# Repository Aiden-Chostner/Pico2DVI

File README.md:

# Pico2DVI

## Story
Recently, I began exploring circuit design, and I liked the idea of creating my own custom graphics card because it sounded like a fun project. After some back and forth of choosing requirements for the GPU, I settled on using a Raspberry Pi Pico as the main processor. It already had a graphics library made for it, which would make adding HDMI support simple. I saw [PicoDVI by Luke Wren](https://github.com/Wren6991/PicoDVI), but I wanted to add more RAM and some extra capabilities. I added 32MB of VRAM (Video Random Access Memory), which is about 250 times less capacity and 36 million times slower than the memory on a modern GPU. (As you can probably tell, I was not going for speed.) The Pico also has Wi-Fi and extra general-purpose pins. That means the card can take in user inputs like a keyboard and output data in ways other than just a display. It can also fetch data (e.g stock market information) from the Internet. I prioritized versatility over speed.

## Specs
* RP2350 Core
* 32 MB VRAM
* HDMI DVI
* Extra I/O
* Subzero Cooler
* Wifi 2.4 GHz

## If you want to build it, I have an [instructables page](https://www.instructables.com/Pico2DVI-the-Graphics-Card-You-Can-Build-Yourself/)!

## Schematic

### I went through a couple variations changing:
* Memory
* Cooling
* Extra I/O Pins

## PCB

### Impedance 
The hardest part about designing the PCB was getting the DVI traces correct. At the clock speeds that DVI runs at, electricity starts to behave unpredictably. The signals start to degrade to the point where they cannot be properly received by the monitor. To correct the signals, I needed to use the impedance calculator in KiCad. It took a couple of attempts through trial and error to correctly calculate the impedance needed for DVI.

## Subzero Cooler

### Peltier Module
For HDMI to work properly the Raspberry Pi needs to be overclocked. This generates excess heat so I designed a subzero cooler. It uses a Peltier module which uses electricity to move heat from one side to the other. Using one on the GPU allows the core temperature to be lower than the room it is in.

## Memory

### Bitbanging
The protocol the memory chips use is called SPI. (Serial Peripheral Interface) Each chip uses four wires on a shared bus with every other chip, which saves valuable GPIO pins from the Raspberry Pi. I decided to bitbang the signals and code them manually. Each instruction, like reading or writing, has a different timing diagram like the one above. I made a function that had modular instructions so I did not have to manually code each one.

# Projects!
## Hello World

When I first got the graphics card working I was so excited. It took four revisions to get the circuit board design right. The months of designing and building finally paid off!

Then, I started work on making a frame to build off of. I first started to work on controlling the cooler. It uses a feedback loop so it can idle at a set temperature. It can even go below zero! Next, I added a overlay that shows all the data of the graphics card, including FPS, clock speed, and more. I also made a simple render script so that the card can display pixels instead of just plain text.

## Conway's Game of Life

Conway's Game of Life is a zero player game where there is a grid with cells. Each cell can either be alive or dead. The eight pixels around a cell are called its neighbors. If there are less than two neighbors, that cell will die. If there are two or three neighbors around a live cell, then it will move on to the next generation. If there are more than three neighbors, it will die. If there are exactly three cells around a dead cell, it becomes alive. These four simple rules create a complex system.

To make the game, I used two screen buffers. One buffer to render to the screen and in the background, I would use the second one to calculate the next generation. Each pixel needs to know its neighbors around it, so I created an indexing system. Each pixel has its own index which I add or subtract a certain value to get the position of the pixels around it. Using the position, it checks whether or not the cell is alive.

## Future

In the future, I want to expand this project by making a couple games like Tetris or maybe Doom. I think a simple raytracing engine would be cool. I have tried making a simple engine in [Shadertoy](https://shadertoy.com) and it was pretty fun. I could even use the memory to make a neural network!

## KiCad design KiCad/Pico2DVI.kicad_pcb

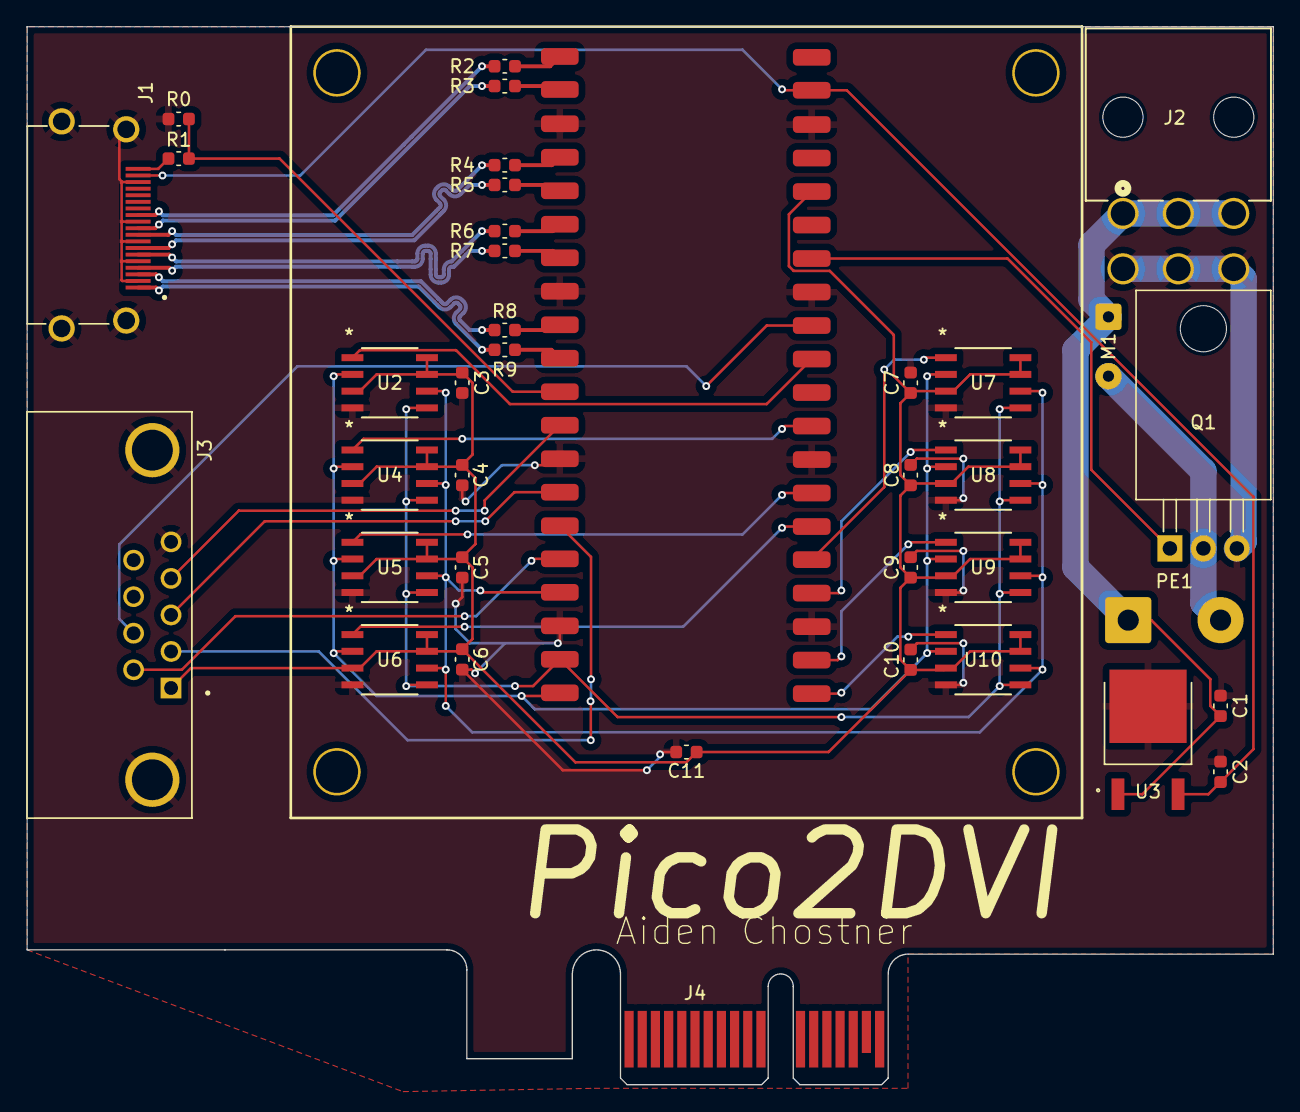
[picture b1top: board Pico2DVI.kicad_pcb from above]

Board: 2 copper layers, 94.5 x 80.2 mm, 38 parts (0 on the bottom side), 40 nets.

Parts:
C1: 0.33 uf; C_0603_1608Metric
C2: 1 uf; C_0603_1608Metric
C3, C4, C5, C6, C7, C8, C9, C10: 0.1; C_0603_1608Metric
C11: 4.7; C_0603_1608Metric
J1: SS-53000-001; STEWART_SS-53000-001
J2: 455580003; CONN_SD-45558-001_MOL
J3: A-DF_09_A_KG-T2S; ASSMANN_A-DF_09_A_KG-T2S
J4: Bus_PCI_Express_x1; BUS_PCIexpress_x1
M1: Fan; SolderWire-0.25sqmm_1x02_P4.5mm_D0.65mm_OD2mm
PE1: PeltierElement; SolderWire-0.75sqmm_1x02_P7mm_D1.25mm_OD3.5mm
Q1: IPP011N03LF2S; TO-220-3_Horizontal_TabDown
R0: 10k; C_0603_1608Metric
R1: 5.1k; C_0603_1608Metric
R2, R3, R4, R5, R6, R7, R8, R9: 270; C_0603_1608Metric
U1: Raspberrypi pico2 w SMD
U2, U4, U5, U6, U7, U8, U9, U10: M95P32-IXMNT/E; SO8N_4X5X1P27_STM-M
U3: L7805CDT-TR; VREG_L7805CDT-TR

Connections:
0+: J1.7, R5.1
0-: J1.9, R4.1
1: J3.2, U1.15 (GP11/_SPI1_TX/I2C1_SCL)
1+: J1.4, R7.1
1-: J1.6, R6.1
2: J3.3, U1.14 (GPI10/SPI1_SCK/I2C1_SDA)
2+: J1.1, R9.1
2-: J1.3, R8.1
3: J3.4, U1.12 (GP9/SPI1_CSn/I2C0_SCL/UART1_RX)
4: J3.6, U1.16 (GP12/SPI1_RX/I2C0_SDA/UART0_TX)
5: J3.7, U1.32 (GP27/ADC1/I2C1_SCL)
+3.3V: C3.1, C4.1, C5.1, C6.1, C7.1, C8.1, C9.1, C10.1, C11.1, J3.1, U1.36 (3V3_OUT), U2.3 (*W-DQ2), U2.7 (*HOLD-DQ3), U2.8 (VCC), U4.3 (*W-DQ2), U4.7 (*HOLD-DQ3), U4.8 (VCC), U5.3 (*W-DQ2), U5.7 (*HOLD-DQ3), U5.8 (VCC), U6.3 (*W-DQ2), U6.7 (*HOLD-DQ3), U6.8 (VCC), U7.3 (*W-DQ2), U7.7 (*HOLD-DQ3), U7.8 (VCC), U8.3 (*W-DQ2), U8.7 (*HOLD-DQ3), U8.8 (VCC), U9.3 (*W-DQ2), U9.7 (*HOLD-DQ3), U9.8 (VCC), U10.3 (*W-DQ2), U10.7 (*HOLD-DQ3), U10.8 (VCC)
+5V: C2.1, J1.18, U1.39 (VSYS), U3.2 (OUTPUT)
+12V: C1.1, J2.1 (12V), J2.2 (12V), J2.3 (12V), M1.1 (+), PE1.1, U3.1 (INPUT)
CLK: U1.17 (GP13/SPI1_CSn/I2C0_SCL/UART0_RX), U2.6 (C), U4.6 (C), U5.6 (C), U6.6 (C), U7.6 (C), U8.6 (C), U9.6 (C), U10.6 (C)
CLK+: J1.10, R3.1
CLK-: J1.12, R2.1
CS0: U1.31 (GP26/ADC0/I2C1_SDA), U2.1 (*S)
CS1: U1.29 (GP22), U4.1 (*S)
CS2: U1.27 (GP21/I2C0_SCL), U5.1 (*S)
CS3: U1.26 (GP20/I2C0_SDA), U6.1 (*S)
CS4: U1.25 (GP19/SPI0_TX/I2C1_SCL), U7.1 (*S)
CS5: U1.24 (GP18/SPI0_SCK/I2C1_SDA), U8.1 (*S)
CS6: U1.22 (GP17/SPI0_CSn/I2C0_SCL/UART0_RX), U9.1 (*S)
CS7: U1.21 (GP16/SPI0_RX/I2C0_SDA/UART0_TX), U10.1 (*S)
D0: U1.19 (GP14/SPI1_SCK/I2C1_SCL), U2.5 (D-DQ0), U4.5 (D-DQ0), U5.5 (D-DQ0), U6.5 (D-DQ0), U7.5 (D-DQ0), U8.5 (D-DQ0), U9.5 (D-DQ0), U10.5 (D-DQ0)
D1: U1.20 (GP15/SPI1_TX/I2C1_SCL), U2.2 (Q-DQ1), U4.2 (Q-DQ1), U5.2 (Q-DQ1), U6.2 (Q-DQ1), U7.2 (Q-DQ1), U8.2 (Q-DQ1), U9.2 (Q-DQ1), U10.2 (Q-DQ1)
GND: C1.2, C2.2, C3.2, C4.2, C5.2, C6.2, C7.2, C8.2, C9.2, C10.2, C11.2, J1.2, J1.5, J1.8, J1.11, J1.17, J1.S1 (SHIELD), J1.S2 (SHIELD__1), J1.S3 (SHIELD__2), J1.S4 (SHIELD__3), J2.4 (GND), J2.5 (Sense_A), J2.6 (GND), J3.5, J3.S1 (SHIELD), J3.S2 (SHIELD__1), Q1.3 (SOURCE), R0.2, U1.3 (GND), U1.8 (GND), U1.13 (GND), U1.18 (GND), U1.23 (GND), U1.28 (GND), U1.33 (GND/AGND), U1.38 (GND), U2.4 (VSS), U3.3 (GROUND), U4.4 (VSS), U5.4 (VSS), U6.4 (VSS), U7.4 (VSS), U8.4 (VSS), U9.4 (VSS), U10.4 (VSS)
HPD: R0.1, R1.2, U1.11 (GP8/SPI1_RX/I2C0_SDA/UART1_TX)
unnamed: J1.19, R1.1
unnamed: M1.2 (-), PE1.2, Q1.2 (DRAIN)
unnamed: R2.2, U1.1 (GP0/I2C0_SDA/UART0_TX)
unnamed: R3.2, U1.2 (GP1_/I2C0_SCL/UART0_RX)
unnamed: R4.2, U1.4 (GP2/SPIO_SCK/I2C1_SDA)
unnamed: R5.2, U1.5 (GP3/SPIO_TX/I2C1SCL)
unnamed: R6.2, U1.6 (GP4/SPIO_RX/I2C0_SDA/_UART1_TX)
unnamed: R7.2, U1.7 (GP5/SPIO_CSn/I2C0_SCL)
unnamed: R8.2, U1.9 (GP6/SPIO_SCK/I2C1_SDA)
unnamed: R9.2, U1.10 (GP7/SPI0_TX/_I2C1_SCL)
PWM: Q1.1 (GATE), U1.34 (GP28/ADC2)

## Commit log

2025-12-29 Rename pcb.png to production/pcb.png
2025-12-29 Rename pcb.png to pcb.png
2025-12-29 Rename schematic.png to images/schematic.png
2025-12-29 Rename Pico2DVI.zip to production/PCB/Pico2DVI.zip
2025-12-29 Rename subzero cooler.png to images/subzero_cooler.png
2025-12-29 Rename subzero cooler.png to subzero_cooler.png
2025-12-29 Update and rename sym-lib-table to KiCad/sym-lib-table
2025-12-29 3d models
2025-12-30 cover image
2025-12-30 Rename main.JPG to main.jpg
2025-12-30 code
2025-12-30 Rename install.txt to Install Instructions.txt
2025-12-30 pictures
